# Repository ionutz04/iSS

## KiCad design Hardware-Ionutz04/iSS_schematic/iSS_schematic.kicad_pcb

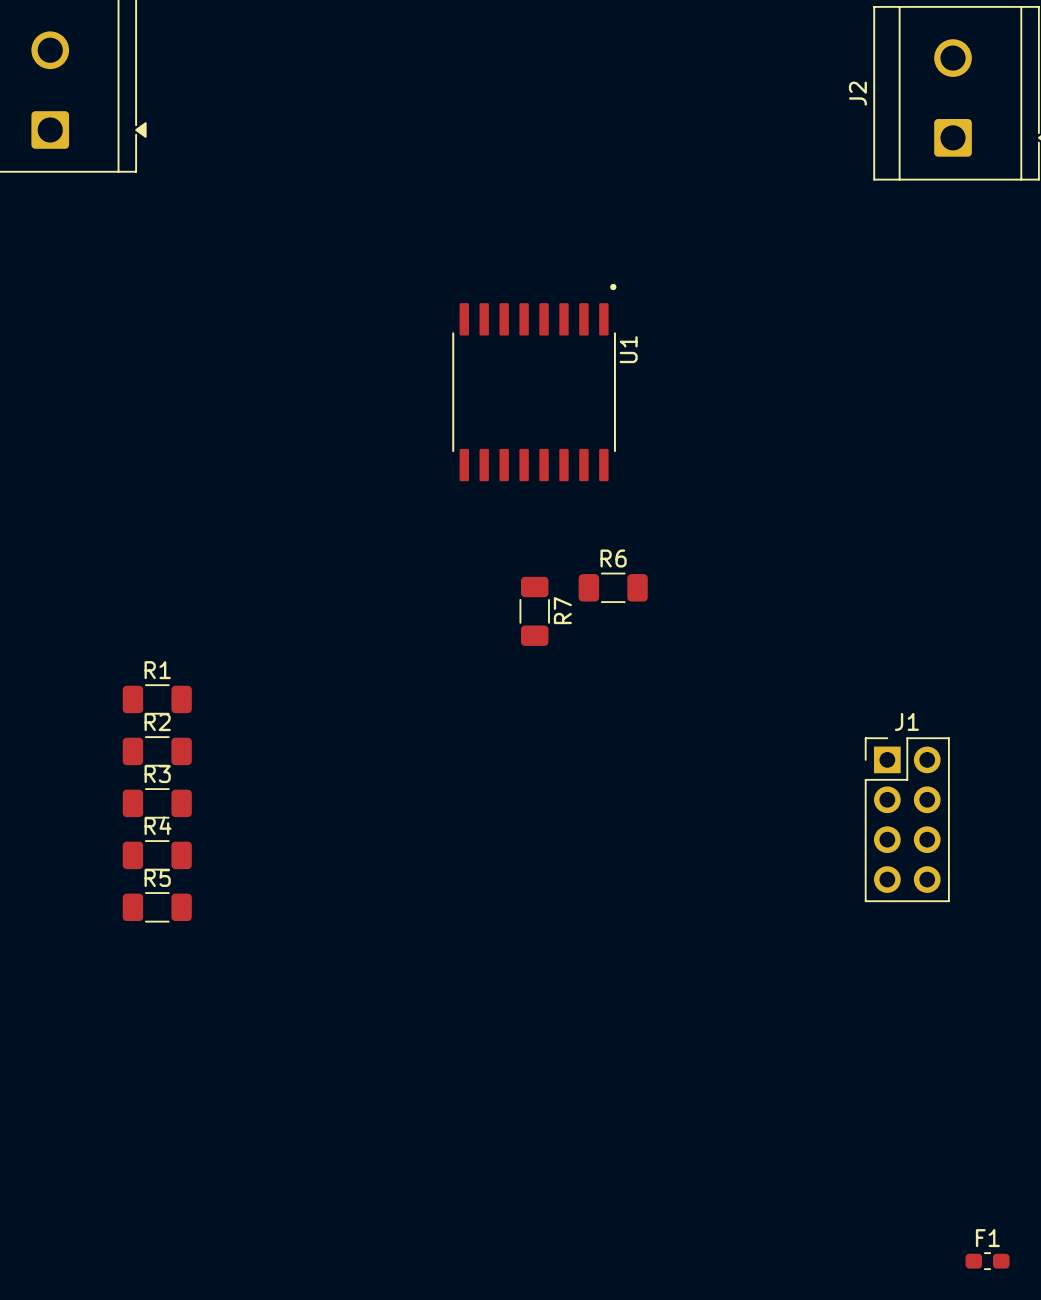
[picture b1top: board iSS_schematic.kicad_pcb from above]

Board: 2 copper layers, 12 parts (0 on the bottom side), 9 nets, no tracks yet.

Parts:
F1: Fuse; Fuse_0603_1608Metric_Pad1.05x0.95mm_HandSolder
J1: Conn_02x04_Row_Letter_First; PinHeader_2x04_P2.54mm_Vertical
J2, J3: Screw_Terminal_01x02; TerminalBlock_CUI_TB007-508-02_1x02_P5.08mm_Horizontal
R1, R2, R4, R5: 1M; R_1206_3216Metric_Pad1.30x1.75mm_HandSolder
R3: 3.9K; R_1206_3216Metric_Pad1.30x1.75mm_HandSolder
R6, R7: 4.7k; R_1206_3216Metric_Pad1.30x1.75mm_HandSolder
U1: ACS37800KMACTR-030B3-I2C; SOIC127P1030X265-16N

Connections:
3.3V: R6.1, R7.1, U1.11 (SCL/SCLK), U1.12 (SDA/MISO), U1.13 (VCC)
NULL: J2.2, J3.2, R1.1
unnamed: F1.2, R5.1
unnamed: R1.2, R2.1
unnamed: R4.1, R5.2
PHIin: F1.1, J2.1, U1.1 (IP+), U1.2 (IP+__1), U1.3 (IP+__2), U1.4 (IP+__3)
PHIout: J3.1, U1.5 (IP-), U1.6 (IP-__1), U1.7 (IP-__2), U1.8 (IP-__3)
VINN: R2.2, R3.1, U1.14 (GND), U1.15 (VINN)
VINP: R3.2, R4.2, U1.16 (VINP)

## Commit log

2025-11-11 Final version of the hardware testing
2025-11-11 Version 1.0 Beta - firmware esp12F
2025-11-11 Version1.0Beta - firmware esp12F
2026-01-08 Beta commit on firmware side of the iSS
2026-01-08 Revert "Beta commit on firmware side of the iSS"
    This reverts commit 418c5d5a18d21a18faee41e17dfe4be9b8e227ae.
2026-01-08 Final commit
